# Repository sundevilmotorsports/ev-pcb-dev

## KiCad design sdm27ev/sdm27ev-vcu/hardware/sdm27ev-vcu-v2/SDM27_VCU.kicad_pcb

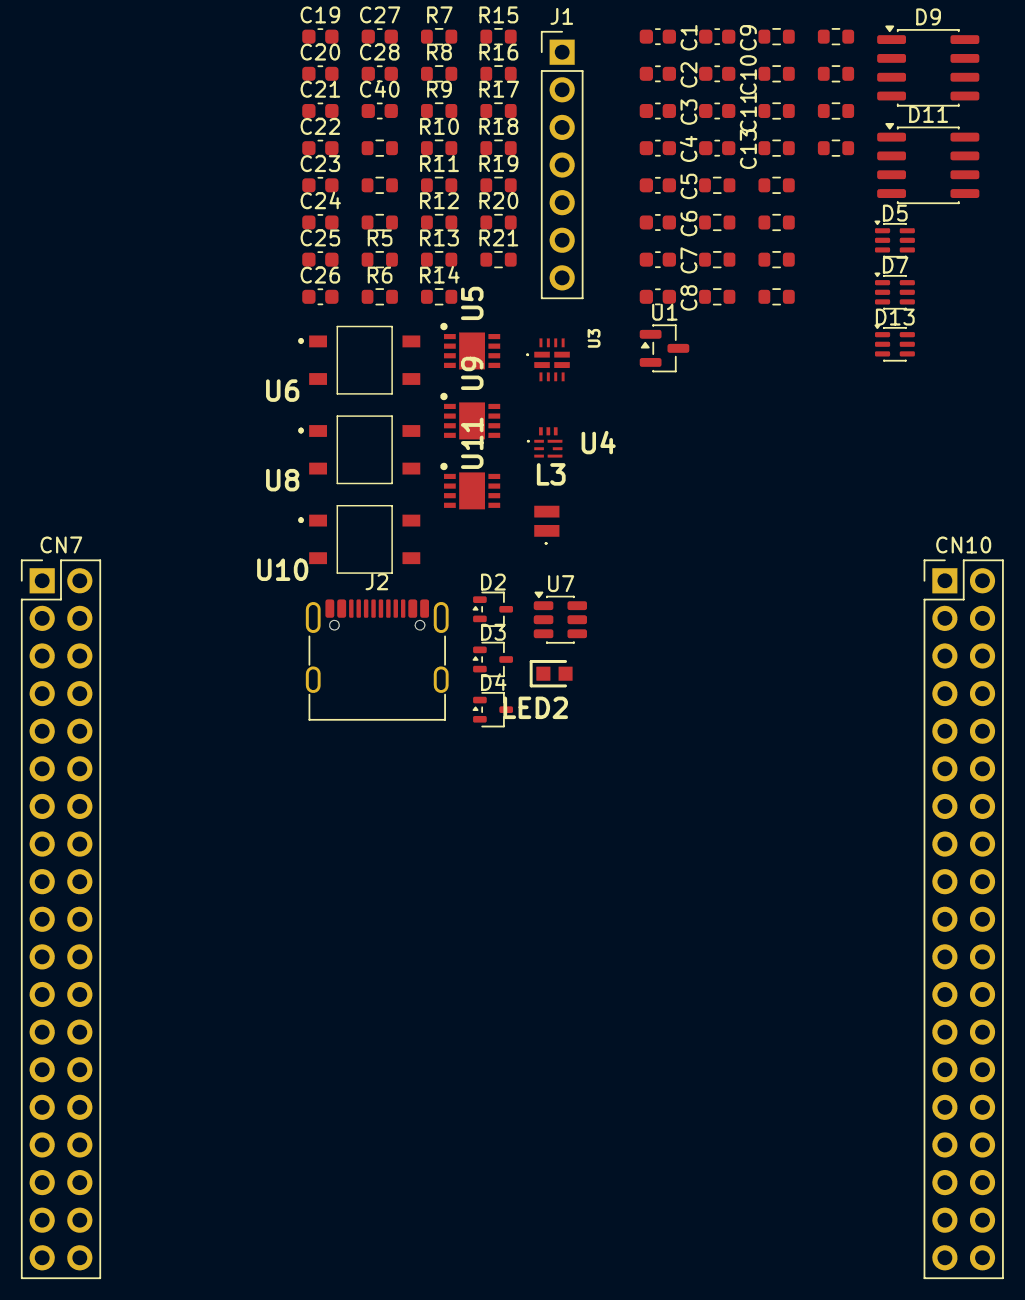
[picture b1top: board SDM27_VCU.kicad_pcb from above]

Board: 2 copper layers, 83 parts (0 on the bottom side), 54 nets, no tracks yet.

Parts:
C1, C2, C3, C4, C5, C6, C7, C8, C9, C10: 2.2n; C_0603_1608Metric
C11, C13: 1u; C_0603_1608Metric
C19: 10nF; C_0603_1608Metric
C20: 1uF 10V 0603; C_0603_1608Metric
C21: 10uF 25V; C_0603_1608Metric
C22: 22uF; C_0603_1608Metric
C23, C24, C25, C26, C27, C28, C40: 100nF; C_0603_1608Metric
CN7: Morpho_CN7; PinHeader_2x19_P2.54mm_Vertical
CN10: Morpho_CN10; PinHeader_2x19_P2.54mm_Vertical
D2, D3, D4: ESDCAN03-2BWY; SOT-323_SC-70
D5, D7, D13: BAV199S-QZ; SOT-363_SC-70-6
D9, D11: SMDA24C-4; SOIC-8_3.9x4.9mm_P1.27mm
J1: WEIPU SA12 7PIN; PinHeader_1x07_P2.54mm_Vertical
J2: USB_C_Receptacle_USB2.0_16P; USB_C_Receptacle_G-Switch_GT-USB-7010ASV
L3: F1C1-201612-2R2M; F1C12016122R2M
LED2: 150060RS75000; LEDC1608X80N
R1, R2, R3: 390; R_0603_1608Metric
R4, R24, R27, R30, R33: 30k; R_0603_1608Metric
R5, R6: 5.1k; R_0603_1608Metric
R7, R8, R9, R10: 5k; R_0603_1608Metric
R11: 63.4k; R_0603_1608Metric
R12: 23.7k; R_0603_1608Metric
R13: 18.2k; R_0603_1608Metric
R14: 10.2k; R_0603_1608Metric
R15: 100k; R_0603_1608Metric
R16: 113k; R_0603_1608Metric
R17: 24.9k; R_0603_1608Metric
R18: 330; R_0603_1608Metric
R19, R20, R21: 100; R_0603_1608Metric
R22, R23, R25, R26, R28, R29, R31, R32, R34, R35: 10k; R_0603_1608Metric
R36: 2.2k; R_0603_1608Metric
U1: MCP1700T-2802E/TT; SOT-23
U3: TPS2121RUXR
U4: TPS62901RPJR
U5, U9, U11: TCAN3403DRBRQ1; SON65P300X300X100-9N-D
U6, U8, U10: TLP175A_TPL,E; TLP266J
U7: USBLC6-2SC6; SOT-23-6

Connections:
+3.3V: C22.1, C23.1, C24.2, C25.1, C26.2, C27.1, C28.2, L3.2, R16.1, R18.1, U4.3 (VOS), U5.3 (VCC), U5.5 (VIO), U9.3 (VCC), U9.5 (VIO), U11.3 (VCC), U11.5 (VIO)
+12V: J1.6, R11.2, R13.2, U3.7 (IN1)
/CAN1_H: D2.2, J1.2, R19.2, U5.7 (CANH)
/CAN1_L: D2.1, J1.1, U5.6 (CANL), U6.4
/CAN1_RX: CN10.3, U5.4 (RXD)
/CAN1_TERM: CN7.38, R1.1
/CAN1_TX: CN10.5, U5.1 (TXD)
/CAN2_H: D3.2, R20.2, U9.7 (CANH)
/CAN2_L: D3.1, U8.4, U9.6 (CANL)
/CAN2_RX: CN10.29, U9.4 (RXD)
/CAN2_TERM: CN7.36, R2.1
/CAN2_TX: CN10.17, U9.1 (TXD)
/CAN3_H: D4.2, R21.2, U11.7 (CANH)
/CAN3_L: D4.1, U10.4, U11.6 (CANL)
/CAN3_RX: CN10.23, U11.4 (RXD)
/CAN3_TERM: CN7.37, R3.1
/CAN3_TX: CN7.17, U11.1 (TXD)
/PWR_LED: LED2.2 (A), R18.2
/USBM_D+: J2.A6 (D+), J2.B6 (D+), U7.6 (I/O1)
/USBM_D-: J2.A7 (D-), J2.B7 (D-), U7.4 (I/O2)
/USB_D+: CN10.12, U7.1 (I/O1)
/USB_D-: CN10.14, U7.3 (I/O2)
APPS1: C2.1, CN7.30, D5.6 (K3A4), R22.2
APPS2: C6.1, CN10.15, D5.3 (K1A2), R29.2
BPS1: C8.1, CN7.34, D7.3 (K1A2), R32.2
BPS2_SPARE: C4.1, CN10.30, D7.6 (K3A4), R26.2
CLAMP_REF: C13.1, D5.2 (K2), D5.5 (K4), D7.2 (K2), D7.5 (K4), D13.2 (K2), R36.1, U1.2 (VO)
E5V: C11.1, CN7.6, U1.3 (VI)
GND: C1.2, C2.2, C3.2, C4.2, C5.2, C6.2, C7.2, C8.2, C9.2, C10.2, C11.2, C13.2, C19.2, C20.2, C21.2, C22.2, C23.2, C24.1, C25.2, C26.1, C27.2, C28.1, C40.1, CN7.8, CN7.19, CN7.20, CN7.22, CN10.9, CN10.20, CN10.32, D2.3, D3.3, D4.3, D5.1 (A1), D5.4 (A3), D7.1 (A1), D7.4 (A3), D13.1 (A1), J1.5, J1.7, J2.A1 (GND), J2.A12 (GND), J2.B1 (GND), J2.B12 (GND), LED2.1 (K), R5.2, R6.2, R7.1, R8.1, R9.1, R10.1, R15.1, R17.2, R23.2, R25.2, R28.2, R31.2, R34.2, R36.2, U1.1 (GND), U3.9 (ST), U3.12 (GND), U4.4 (GND), U4.7 (CONFIG), U5.2 (GND), U5.8 (STB), U5.9 (EP), U6.3, U7.2 (GND), U8.3, U9.2 (GND), U9.8 (STB), U9.9 (EP), U10.3, U11.2 (GND), U11.8 (STB), U11.9 (EP)
unnamed: C1.1, R4.2, R22.1, R23.1
unnamed: C3.1, R24.2, R25.1, R26.1
unnamed: C5.1, R27.2, R28.1, R29.1
unnamed: C7.1, R30.2, R31.1, R32.1
unnamed: C9.1, R33.2, R34.1, R35.1
unnamed: J2.A5 (CC1), R5.1
unnamed: J2.B5 (CC2), R6.1
unnamed: R1.2, U6.1
unnamed: R2.2, U8.1
unnamed: R3.2, U10.1
unnamed: R19.1, U6.6
unnamed: R20.1, U8.6
unnamed: R21.1, U10.6
unnamed: R9.2, R14.1, U3.3 (CP2)
unnamed: R15.2, U3.10 (ILIM)
unnamed: R8.2, R11.1, U3.5 (OV1)
unnamed: R10.2, R12.1, U3.4 (OV2)
unnamed: R7.2, R13.1, U3.6 (PR1)
unnamed: C20.1, U3.11 (SS)
unnamed: C19.1, U4.8 (SS/TR)
unnamed: L3.1, U4.2 (SW)
unnamed: R16.2, R17.1, U4.9 (VSET)
SPARE_AN6: C10.1, CN10.16, D13.6 (K3A4), R35.2
VBUS: C40.2, J2.A4 (VBUS), J2.A9 (VBUS), J2.B4 (VBUS), J2.B9 (VBUS), R12.2, R14.2, U3.2 (IN2), U7.5 (VBUS)
VCC: C21.1, U3.1 (OUT_1), U3.8 (OUT_2), U4.5 (EN), U4.6 (VIN)

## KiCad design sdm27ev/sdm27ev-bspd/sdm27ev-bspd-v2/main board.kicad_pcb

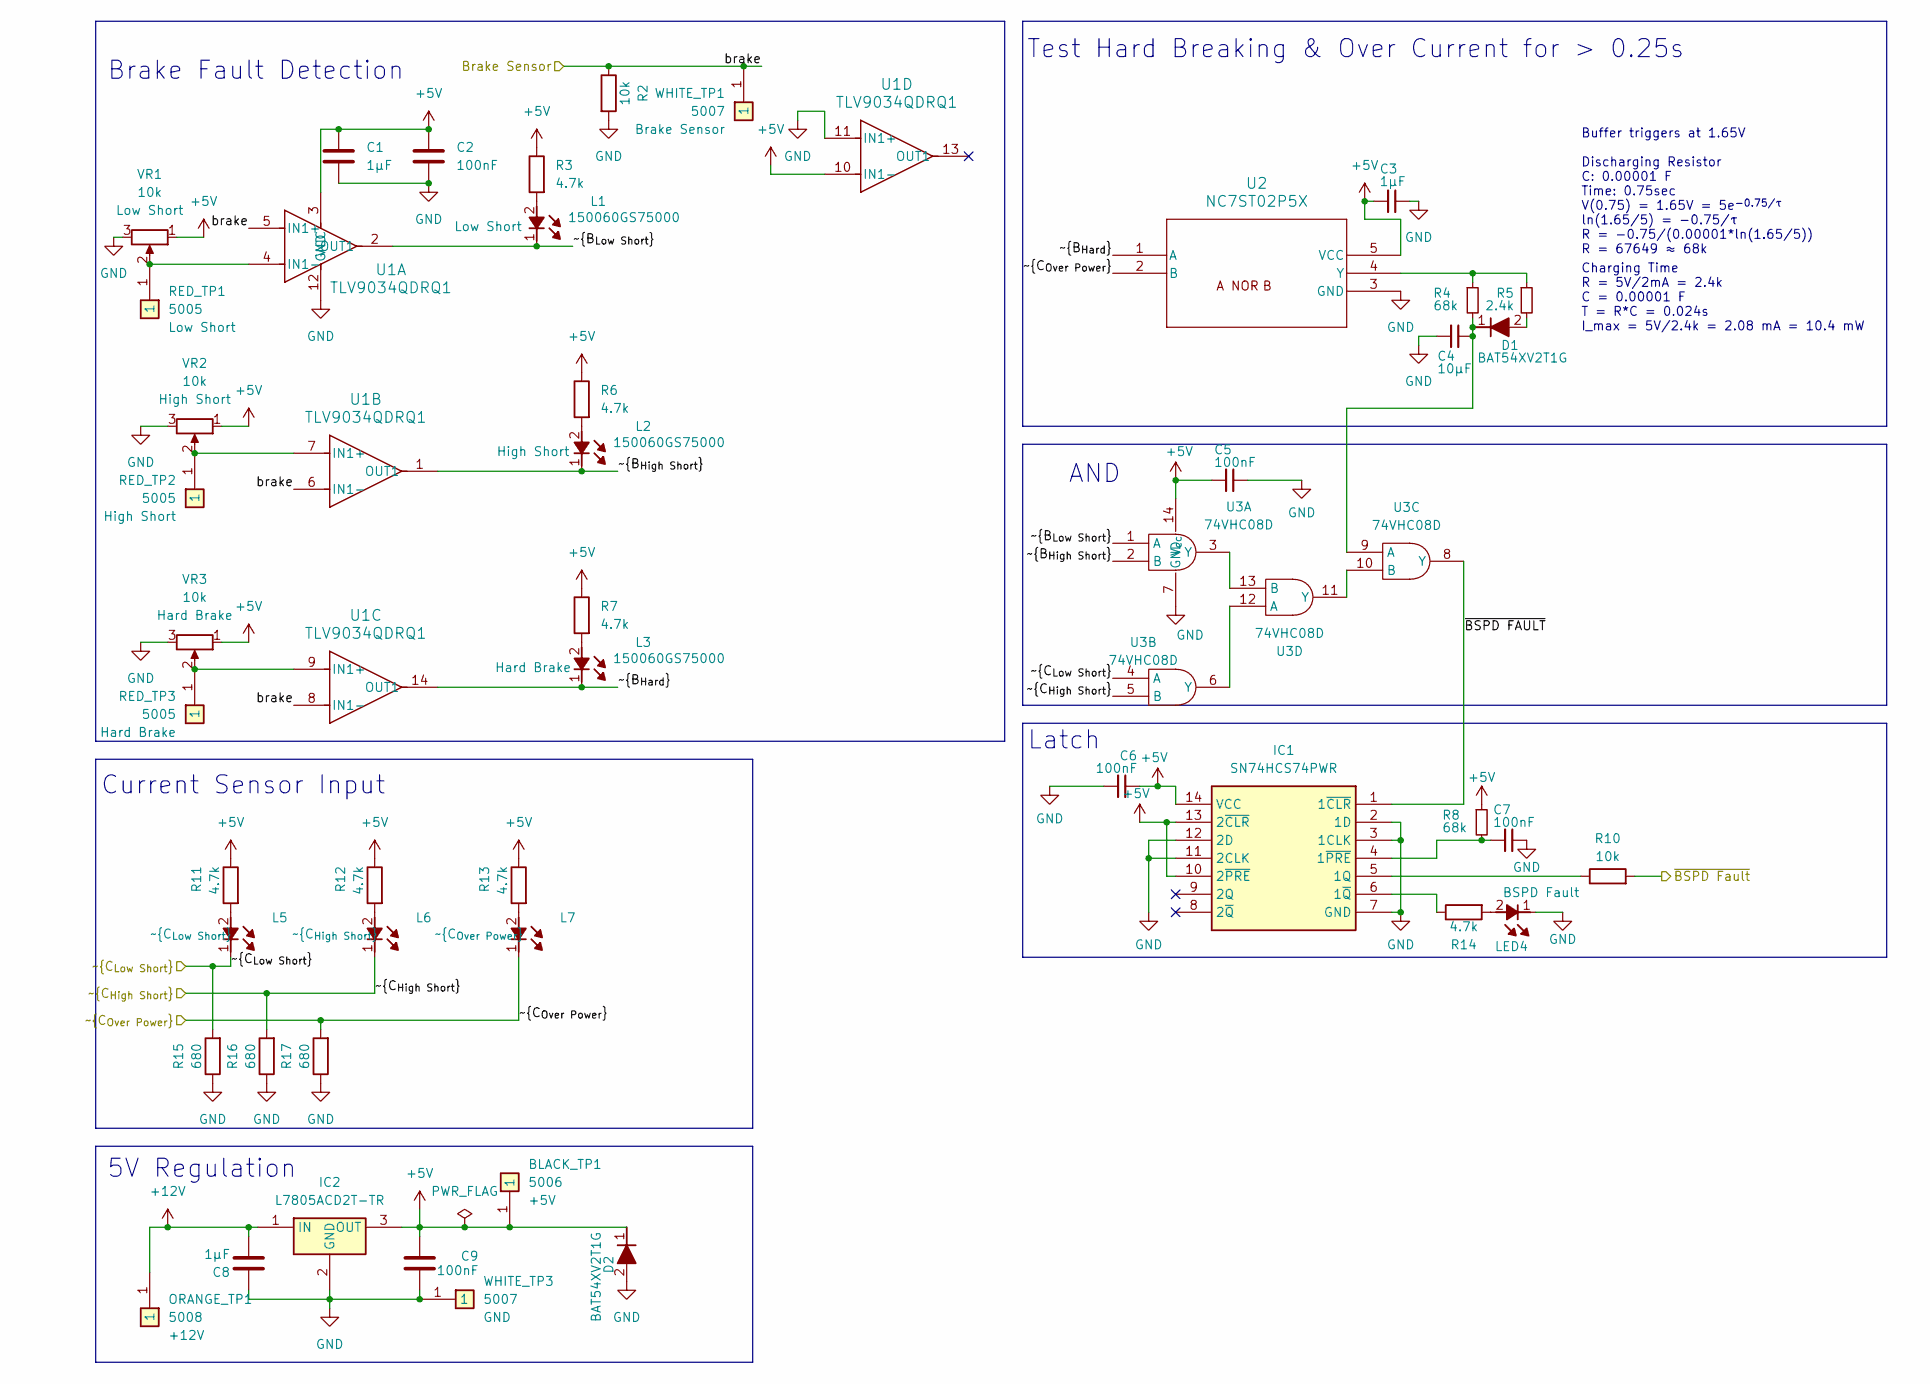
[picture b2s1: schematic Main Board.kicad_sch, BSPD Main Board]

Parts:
BLACK_TP1: 5006; Mouser Part Number 534-5006
C1, C3, C8: 1µF; C_0603_1608Metric
C2, C5, C6, C7, C9: 100nF; C_0603_1608Metric
C4: 10µF; C_0603_1608Metric; Manufacturer_Part_Number CL10A106KP8NNWC; Mouser Part Number 187-CL10A106KP8NNWC
D1, D2: BAT54XV2T1G; SODFL1608X70N; Mouser Part Number 863-BAT54XV2T1G
IC1: SN74HCS74PWR; Mouser Part Number 595-SN74HCS74PWR
IC2: L7805ACD2T-TR; L7805ACD2TTR; Mouser Part Number 511-L7805ACD2T-TR
L1, L2, L3, L5, L6, L7: 150060GS75000; LEDC1608X80N; Mouser Part Number 710-150060GS75000
LED4: 150060GS75000; LEDC1608X80N; Mouser Part Number 710-150060GS75000
ORANGE_TP1: 5008; 5005; Mouser Part Number 534-5008
R2, R10: 10k; R_0603_1608Metric
R3, R6, R7, R11, R12, R13, R14: 4.7k; R_0603_1608Metric
R4, R8: 68k; R_0603_1608Metric
R5: 2.4k; R_0603_1608Metric
R15, R16, R17: 680; R_0603_1608Metric
RED_TP1, RED_TP2, RED_TP3: 5005; Mouser Part Number 534-5005
U1: TLV9034QDRQ1; SOIC-14_3.9x8.7mm_P1.27mm; Manufacturer_Part_Number TLV9034QDRQ1; Mouser Part Number 595-TLV9034QDRQ1
U2: NC7ST02P5X; SC-88A-5_1P35X2P2_ONS; Manufacturer_Part_Number NC7ST02P5X; Mouser Part Number 512-NC7ST02P5X
U3: 74VHC08D; Manufacturer_Part_Number 74VHC08D,118; Mouser Part Number 1727-4348-1-ND
VR1, VR2, VR3: 10k; 3386P1103TLF; Mouser Part Number 652-3386P-1-103TLF
WHITE_TP1, WHITE_TP3: 5007; Mouser Part Number 534-5007

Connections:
+5V: BLACK_TP1.1 (1_1), C1.1, C2.1, C3.1, C5.2, C6.2, C9.2, D2.1 (K), IC1.10 (2~PRE), IC1.13 (2~CLR), IC1.14 (VCC), IC2.3 (OUT), R3.1, R6.1, R7.1, R8.1, R11.1, R12.1, R13.1, U1.3 (VCC), U1.10 (IN1-), U2.5 (VCC), U3.14 (V_{cc}), VR1.1 (CCW), VR2.1 (CCW), VR3.1 (CCW); also elsewhere on the board
+12V: C8.2, IC2.1 (IN), ORANGE_TP1.1 (1_1); also elsewhere on the board
/Main Board/brake: R2.1, U1.5 (IN1+), U1.6 (IN1-), U1.8 (IN1-), WHITE_TP1.1 (1_1); also elsewhere on the board
/Main Board/~BSPD FAULT: IC1.1 (1~CLR), U3.8 (Y)
/Main Board/~BSPD Fault: R10.2; also elsewhere on the board
/Main Board/~B_{Hard}: L3.1 (K), U1.14 (OUT1), U2.1 (A)
/Main Board/~B_{High Short}: L2.1 (K), U1.1 (OUT1), U3.2 (B)
/Main Board/~B_{Low Short}: L1.1 (K), U1.2 (OUT1), U3.1 (A)
/~High Short: L6.1 (K), R16.2, U3.5 (B); also elsewhere on the board
/~Low Short: L5.1 (K), R15.2, U3.4 (A); also elsewhere on the board
/~Over Power: L7.1 (K), R17.2, U2.2 (B); also elsewhere on the board
GND: C1.2, C2.2, C3.2, C4.2, C5.1, C6.1, C7.1, C8.1, C9.1, D2.2 (A), IC1.2 (1D), IC1.3 (1CLK), IC1.7 (GND), IC1.11 (2CLK), IC1.12 (2D), IC2.2 (GND), LED4.1 (K), R2.2, R15.1, R16.1, R17.1, U1.11 (IN1+), U1.12 (GND), U2.3 (GND), U3.7 (GND), VR1.3 (CW), VR2.3 (CW), VR3.3 (CW), WHITE_TP3.1 (1_1); also elsewhere on the board
unnamed: D1.2 (A), R5.2
unnamed: C4.1, D1.1 (K), R4.2, U3.9 (A)
unnamed: IC1.5 (1Q), R10.1
unnamed: C7.2, IC1.4 (1~PRE), R8.2
unnamed: IC1.6 (1~Q), R14.1
unnamed: L1.2 (A), R3.2
unnamed: L2.2 (A), R6.2
unnamed: L3.2 (A), R7.2
unnamed: L5.2 (A), R11.2
unnamed: L6.2 (A), R12.2
unnamed: L7.2 (A), R13.2
unnamed: LED4.2 (A), R14.2
unnamed: RED_TP1.1 (1_1), U1.4 (IN1-), VR1.2 (Wiper)
unnamed: RED_TP2.1 (1_1), U1.7 (IN1+), VR2.2 (Wiper)
unnamed: RED_TP3.1 (1_1), U1.9 (IN1+), VR3.2 (Wiper)
unnamed: R4.1, R5.1, U2.4 (Y)
unnamed: U3.3 (Y), U3.13 (B)
unnamed: U3.6 (Y), U3.12 (A)
unnamed: U3.10 (B), U3.11 (Y)

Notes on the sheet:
Brake Fault Detection
AND
Test Hard Breaking & Over Current for > 0.25s
Current Sensor Input
Charging Time R = 5V/2mA = 2.4k C = 0.00001 F T = R*C = 0.024s I_max = 5V/2.4k = 2.08 mA = 10.4 mW
5V Regulation
Buffer triggers at 1.65V Discharging Resistor C: 0.00001 F Time: 0.75sec V(0.75) = 1.65V = 5e^{-0.75/τ} ln(1.65/5) = -0.75/τ R = -0.75/(0.00001*ln(1.65/5)) R = 67649 ≈ 68k
Latch

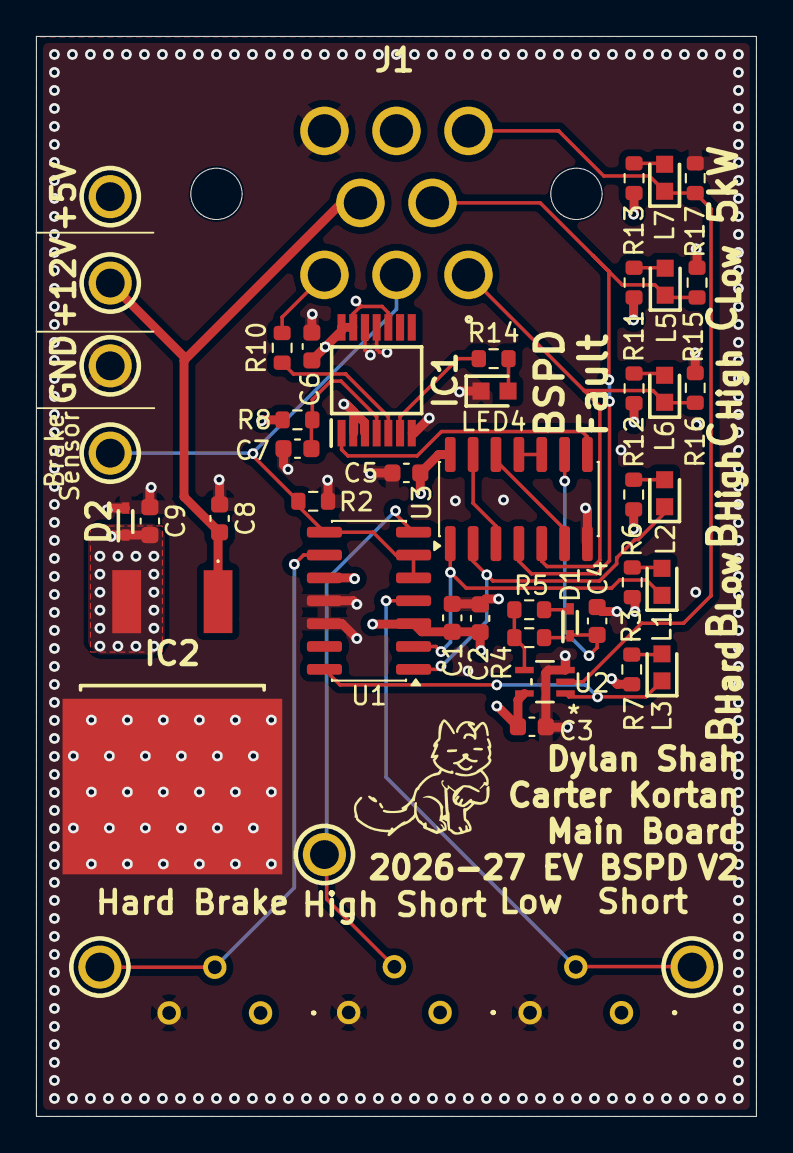
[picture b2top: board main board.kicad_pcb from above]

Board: 4 copper layers, 40.0 x 60.0 mm, 49 parts (0 on the bottom side), 31 nets.

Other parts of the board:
J1: 776280-1

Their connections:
+5V: J1.7 (Pin_5); also elsewhere on the board
+12V: J1.5 (Pin_3); also elsewhere on the board
/Main Board/brake: J1.2 (Pin_4); also elsewhere on the board
/Main Board/~BSPD Fault: J1.3 (Pin_2); also elsewhere on the board
/~High Short: J1.1 (Pin_8); also elsewhere on the board
/~Low Short: J1.4 (Pin_7); also elsewhere on the board
/~Over Power: J1.6; also elsewhere on the board
GND: J1.8 (Pin_1); also elsewhere on the board

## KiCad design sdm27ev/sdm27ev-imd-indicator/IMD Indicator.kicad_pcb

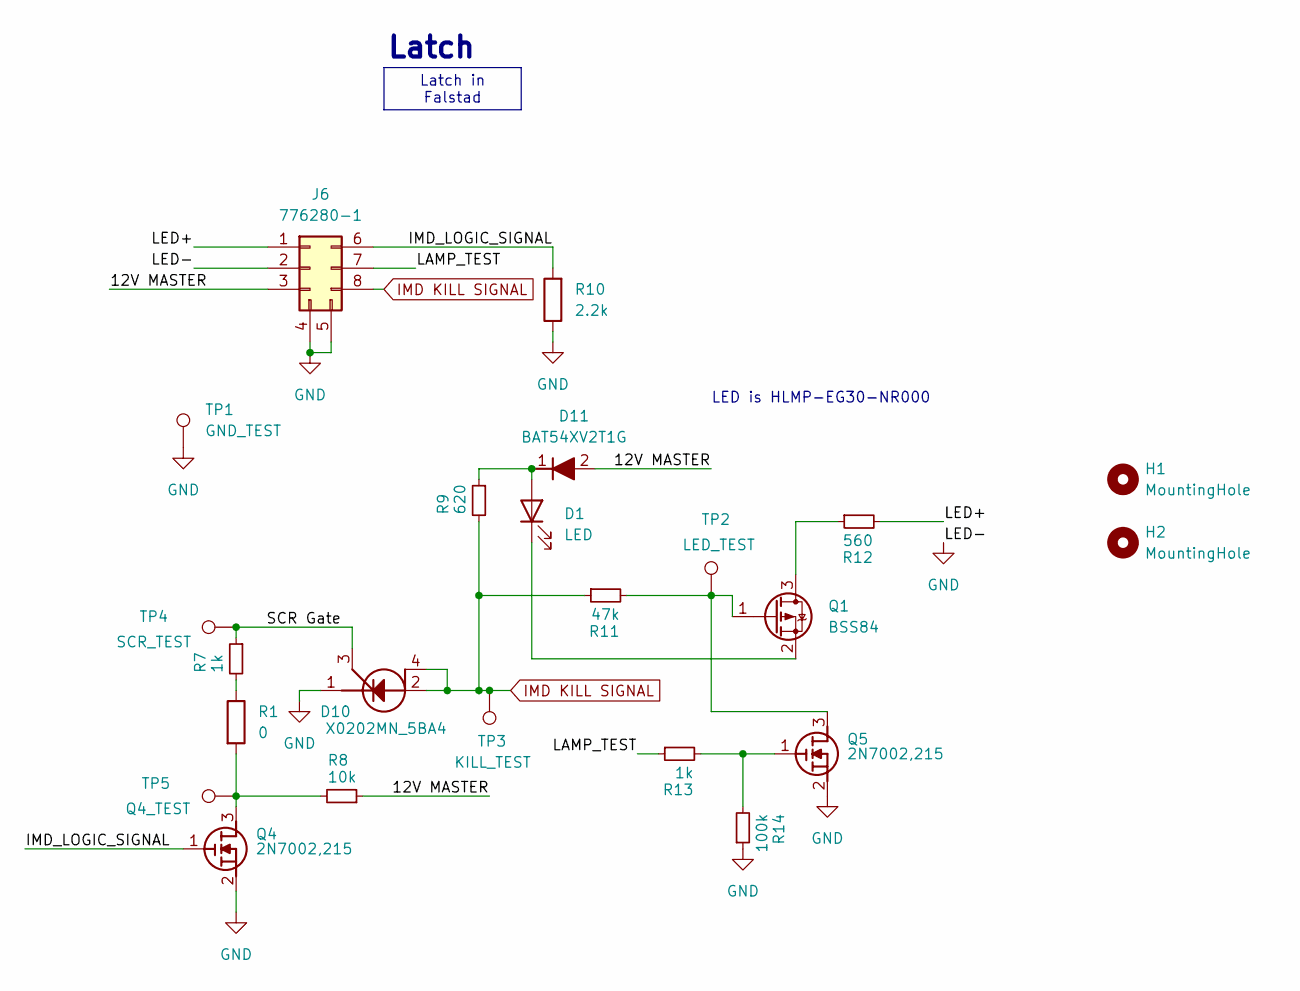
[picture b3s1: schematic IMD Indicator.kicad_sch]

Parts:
D1: LED; LED_0603_1608Metric
D10: X0202MN_5BA4; SOT230P700X190-4N; Mouser Part Number 511-X0202MN
D11: BAT54XV2T1G; SODFL1608X70N; Mouser Part Number 863-BAT54XV2T1G
H1, H2: MountingHole; MountingHole_2.2mm_M2
J6: 776280-1; Mouser Part Number 571-776280-1
Q1: BSS84; SOT-23
Q4, Q5: 2N7002,215; SOT95P230X110-3N; Mouser Part Number 771-2N7002-T/R
R1: 0; R_0603_1608Metric
R7, R13: 1k; R_0603_1608Metric
R8: 10k; R_0603_1608Metric
R9: 620; R_0603_1608Metric
R10: 2.2k; R_0603_1608Metric
R11: 47k; R_0603_1608Metric
R12: 560; R_0603_1608Metric
R14: 100k; R_0603_1608Metric
TP1: GND_TEST; 5007
TP2: LED_TEST; 5007
TP3: KILL_TEST; 5007
TP4: SCR_TEST; 5007
TP5: Q4_TEST; 5007

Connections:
/12V MASTER: D11.2 (A), J6.3, R8.1
/IMD_LOGIC_SIGNAL: J6.6, Q4.1 (G), R10.2
/LAMP_TEST: J6.7, R13.1
/LED+: J6.1, R12.2
/SCR Gate: D10.3 (G), R7.1, TP4.1 (1_1)
GND: D10.1 (K), J6.2, J6.4, J6.5, Q4.2 (S), Q5.2 (S), R10.1, R14.1, TP1.1 (1_1)
IMD KILL SIGNAL: D10.2 (A_1), D10.4 (A_2), J6.8, R9.2, R11.1, TP3.1 (1_1)
unnamed: D1.2 (A), D11.1 (K), R9.1
unnamed: D1.1 (K), Q1.2 (S)
unnamed: Q1.3 (D), R12.1
unnamed: Q1.1 (G), Q5.3 (D), R11.2, TP2.1 (1_1)
unnamed: Q4.3 (D), R1.2, R8.2, TP5.1 (1_1)
unnamed: Q5.1 (G), R13.2, R14.2
unnamed: R1.1, R7.2

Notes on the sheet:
Latch
LED is HLMP-EG30-NR000
Latch in Falstad

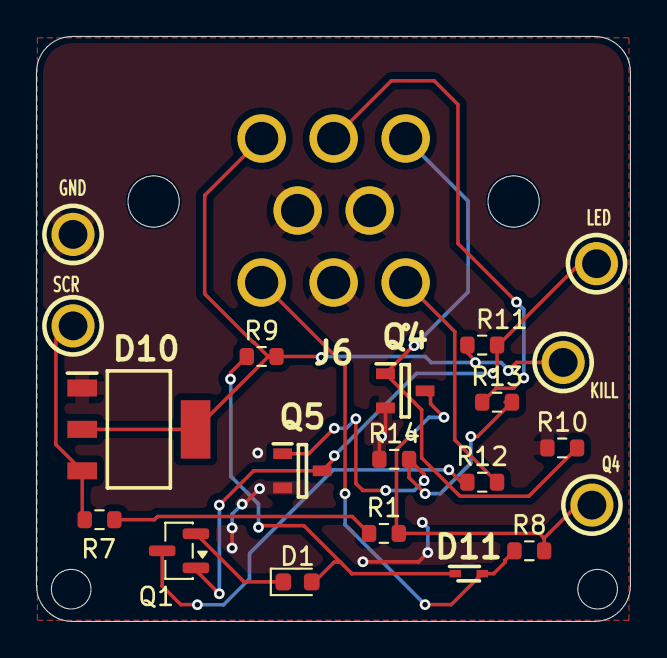
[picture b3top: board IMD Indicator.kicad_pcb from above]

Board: 2 copper layers, 33.0 x 32.5 mm, 23 parts (0 on the bottom side), 14 nets.

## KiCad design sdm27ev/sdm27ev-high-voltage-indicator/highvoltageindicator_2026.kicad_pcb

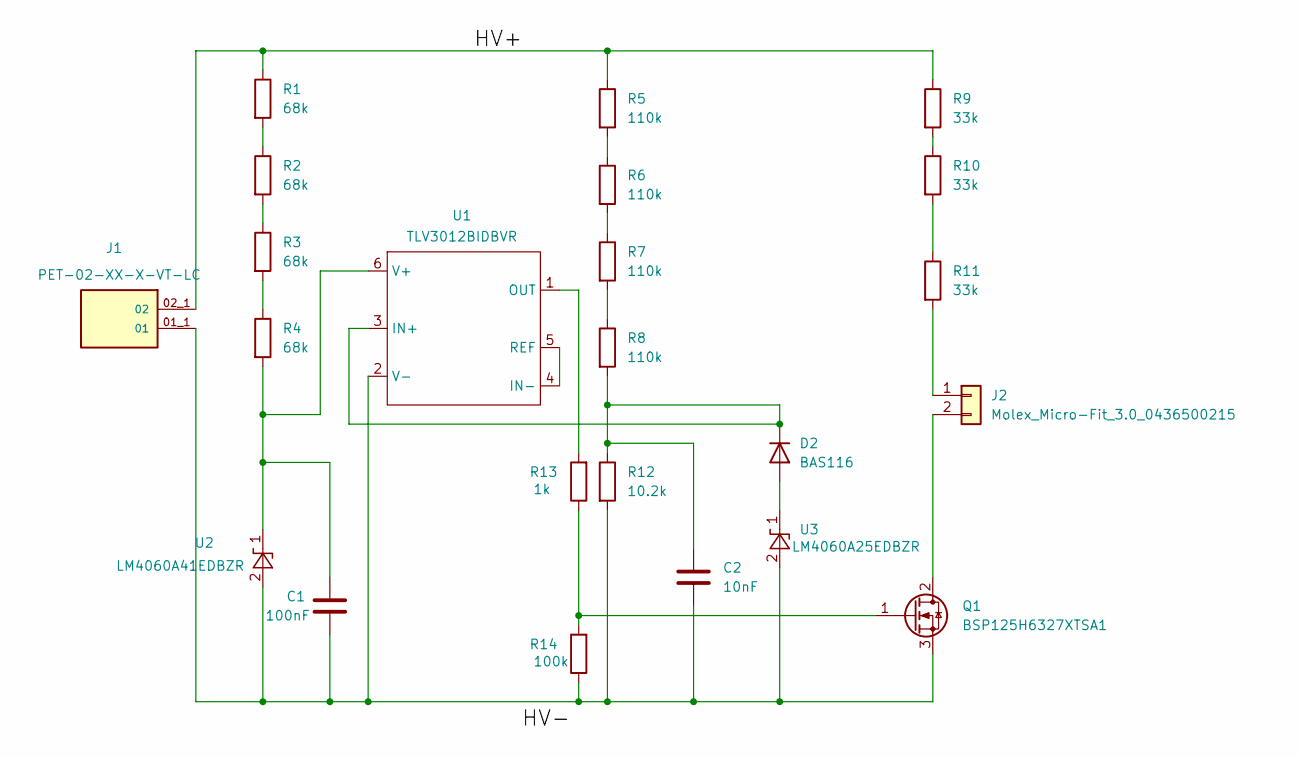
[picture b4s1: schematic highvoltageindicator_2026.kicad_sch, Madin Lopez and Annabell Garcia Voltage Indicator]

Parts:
C1: 100nF; C_1206_3216Metric
C2: 10nF; C_1206_3216Metric
D2: BAS116; SOT-23
J1: PET-02-XX-X-VT-LC; SAMTEC_PET-02-XX-X-VT-LC; PARTREV C
J2: Molex_Micro-Fit_3.0_0436500215; Molex_Micro-Fit_3.0_43650-0215_1x02_P3.00mm_Vertical
Q1: BSP125H6327XTSA1; SOT-223-3_TabPin2
R1, R2, R3, R4: 68k; R_2512_6332Metric
R5, R6, R7, R8: 110k; R_1206_3216Metric
R9, R10, R11: 33k; R_2512_6332Metric
R12: 10.2k; R_1206_3216Metric
R13: 1k; R_1206_3216Metric
R14: 100k; R_1206_3216Metric
U1: TLV3012BIDBVR; SOT-23-6
U2: LM4060A41EDBZR; SOT-23
U3: LM4060A25EDBZR; SOT-23

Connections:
/HV+: J1.02_1 (02), R1.1, R5.1, R9.1
unnamed: D2.2 (A), U3.1 (K)
unnamed: C2.1, D2.1 (K), R8.2, R12.1, U1.3 (IN+)
unnamed: C1.2, C2.2, J1.01_1 (01), Q1.3 (S), R12.2, R14.1, U1.2 (V-), U2.2 (A), U3.2 (A)
unnamed: J2.1, R11.2
unnamed: J2.2, Q1.2 (D)
unnamed: Q1.1 (G), R13.1, R14.2
unnamed: R1.2, R2.1
unnamed: R2.2, R3.1
unnamed: R3.2, R4.1
unnamed: R5.2, R6.1
unnamed: R6.2, R7.1
unnamed: R7.2, R8.1
unnamed: R9.2, R10.1
unnamed: R10.2, R11.1
unnamed: U1.4 (IN-), U1.5 (REF)
unnamed: R13.2, U1.1 (OUT)
unnamed: C1.1, R4.2, U1.6 (V+), U2.1 (K)

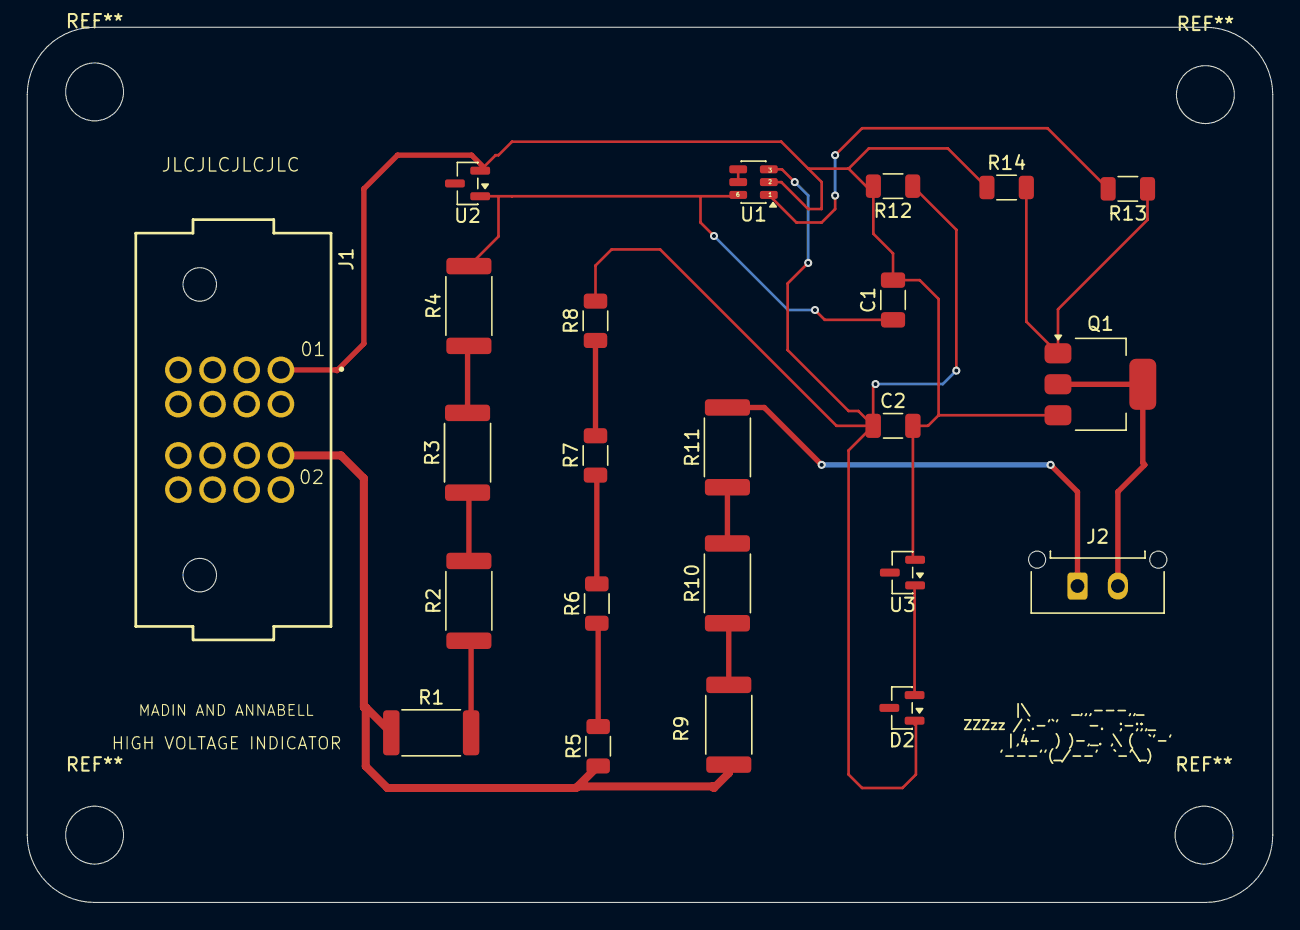
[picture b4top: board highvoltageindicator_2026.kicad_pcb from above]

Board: 4 copper layers, 92.5 x 65.0 mm, 23 parts (0 on the bottom side), 18 nets.

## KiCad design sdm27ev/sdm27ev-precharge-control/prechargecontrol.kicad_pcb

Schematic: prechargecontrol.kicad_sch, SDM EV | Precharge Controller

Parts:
C1: 22uF; C_1210_3225Metric; MPN C3225X7R1H226M250AC
C2: 2.2uF; C_1210_3225Metric; MPN C1210C225K1RACTU
C3, C26, C27, C28, C29, C31: 1uF; C_0603_1608Metric; MPN C0603C105K4RACTU
C4, C9, C12, C13, C15, C17, C19, C20, C22, C30, C58, C59, C60, C61, C62: 100nF; C_0603_1608Metric; MPN C0603C104K5RACTU
C5, C6: 22uF; C_1210_3225Metric; MPN C1210C226K3RACTU
C10, C11, C14, C16: 10uF; C_1210_3225Metric; MPN C1210C106K3RACTU
C18, C21: 100pF; C_0603_1608Metric; MPN C0603C101J5GACTU
C32: 10u 16V; C_1210_3225Metric; MPN C1210C106K4RACTU
C33, C35, C36, C39, C45, C55, C56, C63, C64: 100n; C_0603_1608Metric; MPN C0603C104K5RACTU
C34: 22u 10V; C_1210_3225Metric; MPN C1210C226K8RACTU
C37: 1u; C_0603_1608Metric; MPN C0603C105K4RACTU
C38: 10u 10V; C_0805_2012Metric; MPN C0805C106K8RACTU
C40, C41, C42, C43: 10uF 10V; C_0805_2012Metric; MPN C0805C106K8RACTU
C57: 220nF; C_0805_2012Metric; MPN C0805C224K1RACTU
D1: SS1H10-E3/61T; D_SMA; MPN SS1H10-E3/61T
D2: SMBJ18A; D_SMB; MPN SMBJ18A-E3/52
D3: SMAJ40CA-E3/5A; D_SMA; MPN SMAJ40CA-E3/5A
D6: GREEN; LED_0603_1608Metric; MPN AP1608SGC
D7: YELLOW; LED_0603_1608Metric; MPN APT1608SYCK
D8: RED; LED_0603_1608Metric; MPN AP1608SURCK
D9: GREEN / 3V3; LED_0603_1608Metric; MPN AP1608SGC
D10, D11: 1N4148W; D_SOD-123; MPN 1N4148W-7-F
F1: T1A / 300VDC; Schurter_SPT_Pigtail_P30mm; MPN 0001.2504.PT
F2: T2A / 300VDC; Schurter_SPT_Pigtail_P30mm; MPN 0001.2507.PT
J1: 776280-1; TE_776280-1_8way; MPN 776280-1
J2: PACK_VSENSE; Sabre_43160-0102_P7.49mm_Insulation; MPN 0431600102
J3: DC_LINK_VSENSE; Sabre_43160-0102_P7.49mm_Insulation; MPN 0431600102
J9: RUN / SERVICE; MicroFit_43650_0800_1x08_Edge; MPN 43650-0800
L1: 22uH; L_Coilcraft_XAL6060-XXX; MPN XAL6060-223MEC
L2: 2.2uH XAL4020-222MEC; L_Coilcraft_XAL4020-XXX; MPN XAL4020-222MEC
Q1: IRL640PBF; TO-220-3_Vertical; MPN IRL640PBF
Q2: IRL540NPBF; TO-220-3_Vertical; MPN IRL540NPBF
Q4, Q5: BC847B; SOT-23; MPN BC847B,215
R1: 0R; R_1206_3216Metric; MPN CRCW12060000Z0EA
R2, R104, R108: 100k; R_0603_1608Metric; MPN CRCW0603100KFKEA
R3: 24.9k; R_0603_1608Metric; MPN CRCW060324K9FKEA
R4, R5, R18, R19, R23, R24, R25, R26, R101, R110, R111, R115: 10k; R_0603_1608Metric; MPN CRCW060310K0FKEA
R7, R8: 100; R_0603_1608Metric; MPN CRCW0603100RFKEA
R10, R11, R12, R13: 1k; R_0603_1608Metric; MPN CRCW06031K00FKEA
R14, R15, R16, R17, R100: 2.2k; R_0603_1608Metric; MPN CRCW06032K20FKEA
R21, R22: 22; R_0603_1608Metric; MPN CRCW060322R0FKEA
R27, R28, R29, R30: 2.74k 0.1%; R_0603_1608Metric; MPN RT0603BRD072K74L
R31, R32, R33, R34: 10.0k 0.1%; R_0603_1608Metric; MPN RT0603BRD0710KL
R35, R36, R37, R38: 20.0k 0.1%; R_0603_1608Metric; MPN RT0603BRD0720KL
R99: 47k; R_0603_1608Metric; MPN CRCW060347K0FKEA
R102, R103, R106, R107: 10k / 0.25W; R_1206_3216Metric; MPN CRCW120610K0FKEA
R105, R109, R113, R114: 4.7k; R_0603_1608Metric; MPN CRCW06034K70FKEA
R112: 330; R_0603_1608Metric; MPN CRCW0603330RFKEA
R116, R117, R118, R119: 66.5R 0.1%; R_0603_1608Metric; MPN RT0603BRD0766R5L
TP1: SDC_COIL; TestPoint_Pad_D1.5mm
TP2, TP4: TestPoint_Pad_D1.5mm
TP3, TP5, TP6: TestPoint; TestPoint_Pad_D1.5mm
TP7: PRECHARGE_CMD; TestPoint_Pad_D1.5mm
TP8: MAIN_CMD; TestPoint_Pad_D1.5mm
U1: LMR36510ADDAR; LMR36510_DDA0008B; MPN LMR36510ADDAR
U2: ESP32-C3-WROOM-02-H4; ESP32_C3_WROOM_02_Edge; MPN ESP32-C3-WROOM-02-H4
U3, U4: UCC12050DVER; DVE0016A; MPN UCC12050DVER
U5, U6: AMC0381D06QDFXRQ1; SSOP15_DFX_TEX; MPN AMC0381D06QDFXRQ1
U7: TPS62162QDSGRQ1; Texas_DSG0008A_WSON-8-1EP_2x2mm_P0.5mm_EP0.9x1.6mm_ThermalV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; MPN TPS62162QDSGRQ1
U8: UCC27524AQDRQ1; SOIC-8_3.9x4.9mm_P1.27mm; MPN UCC27524AQDRQ1
U9: STM811TW16F; SOT-143; MPN STM811TW16F
U11: TLV9064QPWRQ1; TSSOP-14_4.4x5mm_P0.65mm; MPN TLV9064QPWRQ1
U19: STM811LW16F; SOT-143; MPN STM811LW16F
U20, U24: SN74LVC1G11IDCKRQ1; SOT-363_SC-70-6; MPN SN74LVC1G11IDCKRQ1
U21: SN74LVC2G14IDCKRQ1; SOT-363_SC-70-6; MPN SN74LVC2G14IDCKRQ1
U22: SN74LVC1G74DCUR; VSSOP-8_2.3x2mm_P0.5mm; MPN SN74LVC1G74DCUR
U23: SN74HCS11PWR; TSSOP-14_4.4x5mm_P0.65mm; MPN SN74HCS11PWR
U25: PAC1944; PAC1944_4MX; MPN PAC1944T-E/4MX

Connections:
+3V3: C19.1, C22.1, C27.1, C29.1, C34.1, C35.1, C36.1, C38.1, C39.1, C45.1, C56.1, C60.1, C61.1, C62.1, C63.1, C64.1, J9.4, L2.2, R13.2, R19.1, R24.1, R25.1, R26.1, R105.1, R109.1, R112.1, R113.1, R114.1, TP2.1 (1_1), U2.1 (3V3), U5.14 (VDD2), U6.14 (VDD2), U7.6 (VOS), U9.4 (VCC), U11.4 (V+), U20.5 (VCC), U21.5 (VCC), U22.2 (D), U22.7 (~PRE), U22.8 (VCC), U23.4 (2B), U23.5 (2C), U23.11 (3C), U23.14 (VCC), U24.5 (VCC), U24.6, U25.2 (VDD), U25.16 (~PWRDN)
+5V: C5.1, C6.2, C9.2, C10.2, C13.2, C14.2, C30.1, C31.1, C32.1, C33.1, C55.1, L1.1, R2.2, TP3.1 (1_1), U3.1 (EN), U3.3 (VINP), U4.1 (EN), U4.3 (VINP), U7.2 (VIN), U8.6 (VDD), U19.3 (~MR), U19.4 (VCC)
/DC_ISO_5V: C15.2, C16.2, C20.1, C28.1, U4.13 (SEL), U4.14 (VISO), U6.5 (VDD1)
/DC_ISO_GND: C15.1, C16.1, C20.2, C21.2, C28.2, J3.2, U4.9 (GNDS), U4.10 (NCS), U4.11 (NCS), U4.12 (NCS), U4.15 (GNDS), U4.16 (GNDS), U6.2 (SNSN), U6.6 (GND1)
/MAIN_GATE_DRIVE: R8.2, U8.5 (OUTB)
/PACK_ISO_5V: C11.2, C12.2, C17.1, C26.1, U3.13 (SEL), U3.14 (VISO), U5.5 (VDD1)
/PACK_ISO_GND: C11.1, C12.1, C17.2, C18.2, C26.2, J2.2, U3.9 (GNDS), U3.10 (NCS), U3.11 (NCS), U3.12 (NCS), U3.15 (GNDS), U3.16 (GNDS), U5.2 (SNSN), U5.6 (GND1)
/PRE_GATE_DRIVE: R7.2, U8.7 (OUTA)
ALL_CLEAR_N: R110.1, U20.6, U22.6 (~CLR), U24.4
ARM_CLEAN: U20.1, U22.1 (CLK), U23.6 (2Y)
ARM_REQUALIFIED: U20.3, U22.5 (Q)
BOOT_N: J9.5, R26.2, U2.8 (GPIO9)
BUCK_EN: R99.1, U7.3 (EN), U19.2 (~RESET), U24.1
BUF_DN: R30.1, U11.13 (-), U11.14
BUF_DP: R29.1, U11.8, U11.9 (-)
BUF_PN: R28.1, U11.6 (-), U11.7
BUF_PP: R27.1, U11.1, U11.2 (-)
CABLE_DM: J9.2, R21.1
CABLE_DP: J9.3, R22.1
DC_OUTN: R34.1, U6.10 (OUTN)
DC_OUTP: R33.1, TP6.1 (1_1), U6.11 (OUTP)
DIV_DN: R34.2, R38.1, U11.12 (+)
DIV_DP: R33.2, R37.1, U11.10 (+)
DIV_PN: R32.2, R36.1, U11.5 (+)
DIV_PP: R31.2, R35.1, U11.3 (+)
DRIVER_ENABLE: R16.1, R17.1, U8.1 (ENA), U8.8 (ENB), U20.4
ESP_EN: C37.1, R23.2, U2.2 (EN/CHIP_PU)
GLV_12V_IN: F1.2, J1.1 (GLV+)
GND: C1.2, C2.2, C3.2, C5.2, C6.1, C9.1, C10.1, C13.1, C14.1, C19.2, C22.2, C27.2, C29.2, C30.2, C31.2, C32.2, C33.2, C34.2, C35.2, C36.2, C37.2, C38.2, C39.2, C40.2, C41.2, C42.2, C43.2, C45.2, C55.2, C56.2, C57.2, C58.2, C59.2, C60.2, C61.2, C62.2, C63.2, C64.2, D2.2 (A), D6.1 (K), D7.1 (K), D8.1 (K), D9.1 (K), D10.2 (A), D11.2 (A), J1.2 (GND), J9.1, Q1.3 (S), Q2.3 (S), Q4.2 (E), Q5.2 (E), R3.1, R4.1, R5.1, R14.2, R15.2, R16.2, R17.2, R18.2, R35.2, R36.2, R37.2, R38.2, R99.2, R100.2, R101.2, R104.2, R108.2, R110.2, R111.2, R115.2, R116.2, R117.2, R118.2, R119.2, TP4.1 (1_1), U1.1 (PGND), U1.9 (PAD), U2.9 (GND), U2.19 (GND), U3.2 (GNDP), U3.4 (SYNC), U3.6 (NCP), U3.7 (NCP), U3.8 (NCP), U4.2 (GNDP), U4.4 (SYNC), U4.6 (NCP), U4.7 (NCP), U4.8 (NCP), U5.9 (GND2), U6.9 (GND2), U7.1 (PGND), U7.4 (AGND), U7.5 (FB), U7.9 (PAD), U8.3 (GND), U9.1 (GND), U11.11 (V-), U19.1 (GND), U20.2 (GND), U21.2 (GND), U22.4 (GND), U23.7 (GND), U24.2 (GND), U25.1 (SLOW/ALERT1), U25.3 (GND), U25.6 (ADDRSEL), U25.7 (SENSE3-), U25.9 (SENSE4-), U25.12 (SENSE1-), U25.14 (SENSE2-), U25.17 (EP_NC)
KEY_FEED: J9.7, R112.2
LED_RED_CMD: R12.2, U2.12 (GPIO21/U0TXD)
MAIN_CMD: R11.2, R15.1, TP8.1 (1_1), U2.10 (GPIO10), U8.4 (INB)
MAIN_SW: J1.6 (MAIN_SW), Q2.2 (D)
MEAS_DN: C43.1, R30.2, R119.1, U25.10 (SENSE4+)
MEAS_DP: C42.1, R29.2, R118.1, U25.8 (SENSE3+)
MEAS_PN: C41.1, R28.2, R117.1, U25.13 (SENSE2+)
MEAS_PP: C40.1, R27.2, R116.1, U25.11 (SENSE1+)
MEAS_SCL: R114.2, U2.17 (GPIO1/ADC1_CH1/XTAL_32K_N), U25.4 (SCL)
MEAS_SDA: R113.2, U2.18 (GPIO0/ADC1_CH0/XTAL_32K_P), U25.5 (SDA)
unnamed: D1.2 (A), F1.1
unnamed: C1.1, D1.1 (K), D2.1 (K), R1.2
unnamed: D6.2 (A), R10.1
unnamed: D7.2 (A), R11.1
unnamed: D8.2 (A), R12.1
unnamed: D9.2 (A), R13.1
unnamed: D10.1 (K), Q4.1 (B), R103.2, R104.1
unnamed: D11.1 (K), Q5.1 (B), R107.2, R108.1
unnamed: J2.1, U5.1 (HVIN)
unnamed: J3.1, U6.1 (HVIN)
unnamed: Q1.1 (G), R4.2, R7.1
unnamed: Q2.1 (G), R5.2, R8.1
unnamed: R102.2, R103.1
unnamed: R106.2, R107.1
unnamed: C4.1, U1.7 (BOOT)
unnamed: C2.1, C57.1, R1.1, U1.2 (VIN), U1.3 (EN)
unnamed: R2.1, R3.2, U1.5 (FB)
unnamed: C4.2, L1.2, U1.8 (SW)
unnamed: C3.1, U1.6 (VCC)
unnamed: C18.1, U5.4 (SNSP)
unnamed: C21.1, U6.4 (SNSP)
unnamed: L2.1, U7.7 (SW)
OUTPUT_ARM: R100.1, U2.11 (GPIO20/U0RXD), U23.3 (2A)
PACK_OUTN: R32.1, U5.10 (OUTN)
PACK_OUTP: R31.1, TP5.1 (1_1), U5.11 (OUTP)
PAC_GPIO_IDLE: R115.1, U25.15 (GPIO/ALERT2)
PRECHARGE_CMD: R10.2, R14.1, TP7.1 (1_1), U2.5 (GPIO6), U8.2 (INA)
PRECHARGE_SW: D3.2 (A2), J1.5 (PRE_SW), Q1.2 (D)
RAIL_OK: R18.1, R23.1, U9.2 (~RESET), U23.1 (1A)
RESET_REQ: R19.2, U9.3 (~MR)
RUN_A: J9.6, R101.1, U23.9 (3A)
RUN_B: J9.8, R111.1, U23.10 (3B)
RUN_PERMISSION: U23.2 (1B), U23.8 (3Y)
SDC_12V_COIL: D3.1 (A1), F2.1, J1.4 (COIL+_OUT), R102.1, TP1.1 (1_1)
SDC_12V_IN: F2.2, J1.3 (SDC_IN)
SDC_N: C58.1, Q4.3 (C), R105.2, U21.1 (1A)
SDC_PRESENT: U2.4 (GPIO5/ADC2_CH0), U21.6 (1Y), U23.13 (1C)
SERVICE_CLEAR_N: U23.12 (1Y), U24.3
START_12V: J1.7 (START_12V), R106.1
START_N: C59.1, Q5.3 (C), R109.2, U21.3 (2A)
START_REQUEST: U2.6 (GPIO7), U21.4 (2Y)
TWAI_RX: R25.2, U2.7 (GPIO8)
TWAI_TX: R24.2, U2.16 (GPIO2/ADC1_CH2)
USB_DM: R21.2, U2.13 (GPIO18/USB_D-)
USB_DP: R22.2, U2.14 (GPIO19/USB_D+)

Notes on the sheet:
ROM download: hold J9.5 low
J3 / U4 / U6 use DC_ISO on the link side.
06 DC-link sense
13 Test points
and qualify true ≥90% before MAIN.
09 P105 precharge
15 Fresh ARM edge and requalification
Hardware permission
CONTROL & ACTUATION
U2 issues commands. U20 qualifies the common enable. U8 drives the low-side switches.
Require a fresh start after SDC loss or
Keep both isolated returns separate from GLV GND.
Input and enable pull-downs
J1.4 red (+) • J1.6 black switched return
05 PACK sense
08 ESP32-C3 controller
Dual gate driver
SERVICE / DEBUG
16 Common clear
service. Validate all four measurements
conditions prevents coil energization.
U9 asserts RAIL_OK after the reset delay.
Boot, reset and rail bypass
J2 / U3 / U5 use PACK_ISO on the pack side.
GPIO2 and GPIO8 sample high at reset. Release TWAI RX during strapping.
11 RUN / isolated SERVICE cable
J1.4 coil positive • J1.5 switched return
Precharge sequence
USB series resistors
POWER
SDM EV / PRECHARGE CONTROLLER
Four VSENSE inputs, address 0x10.
J9.4 is the +3.3 V target reference. Legacy RESET cables are incompatible.
RUN key and default bias
U25 bypass and bus bias
01 Vehicle harness
U20 requires all three inputs:
3.3 V supervision
12 Indicators
02 Controller / GLV protection

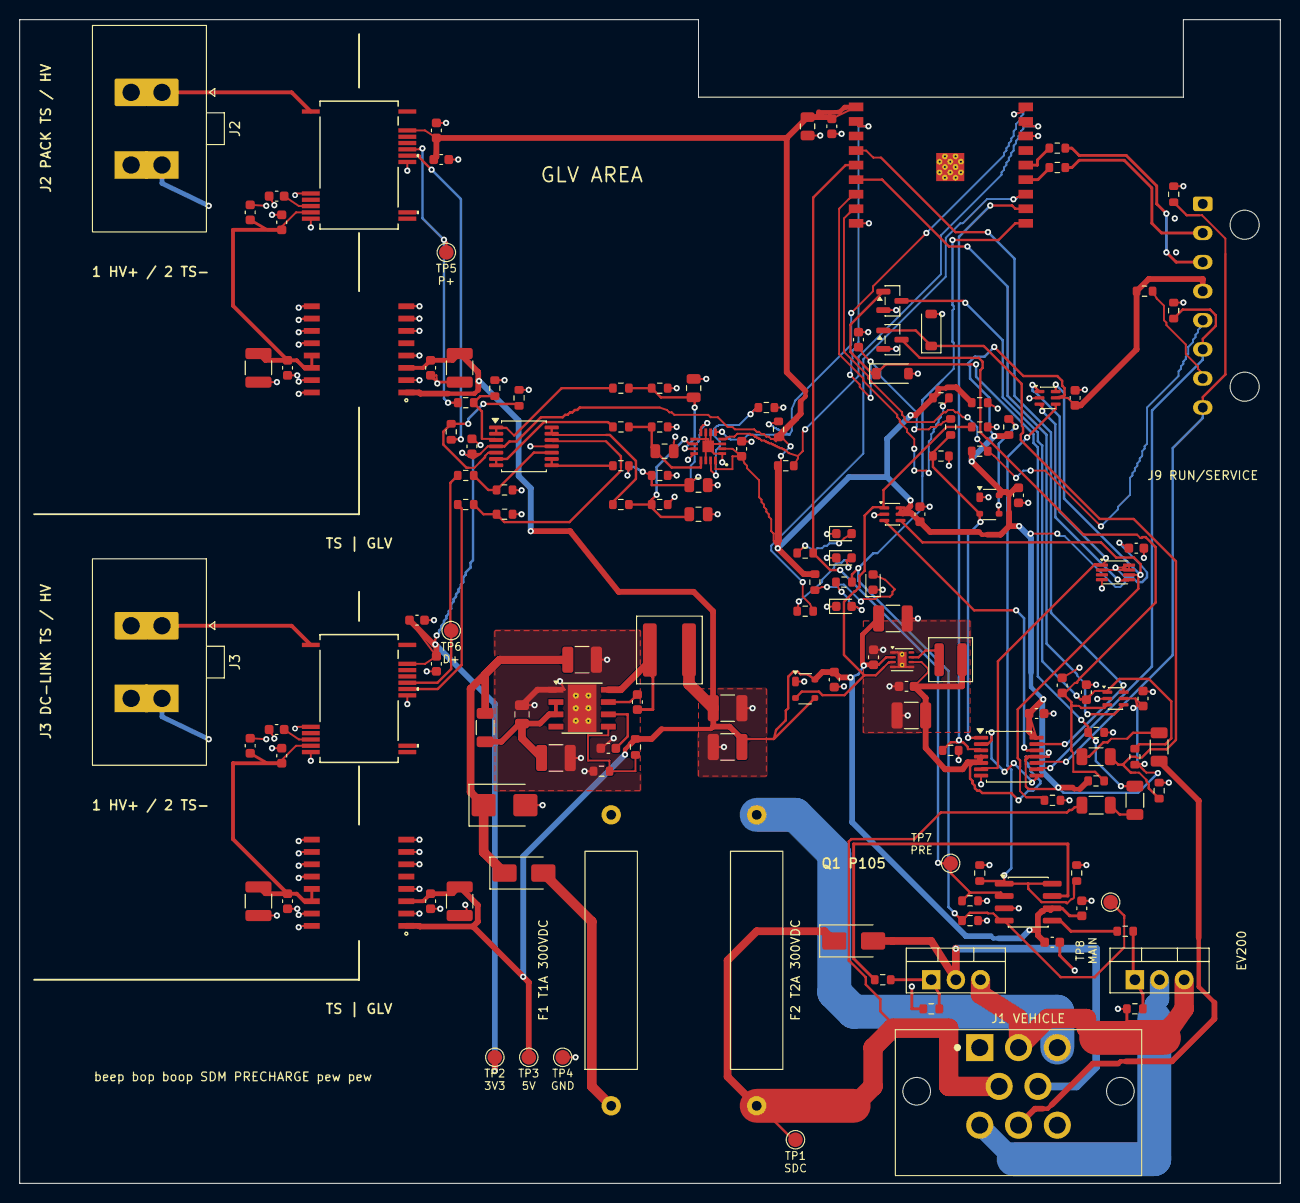
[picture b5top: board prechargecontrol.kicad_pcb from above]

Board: 4 copper layers, 130.0 x 120.0 mm, 151 parts (0 on the bottom side), 84 nets.
